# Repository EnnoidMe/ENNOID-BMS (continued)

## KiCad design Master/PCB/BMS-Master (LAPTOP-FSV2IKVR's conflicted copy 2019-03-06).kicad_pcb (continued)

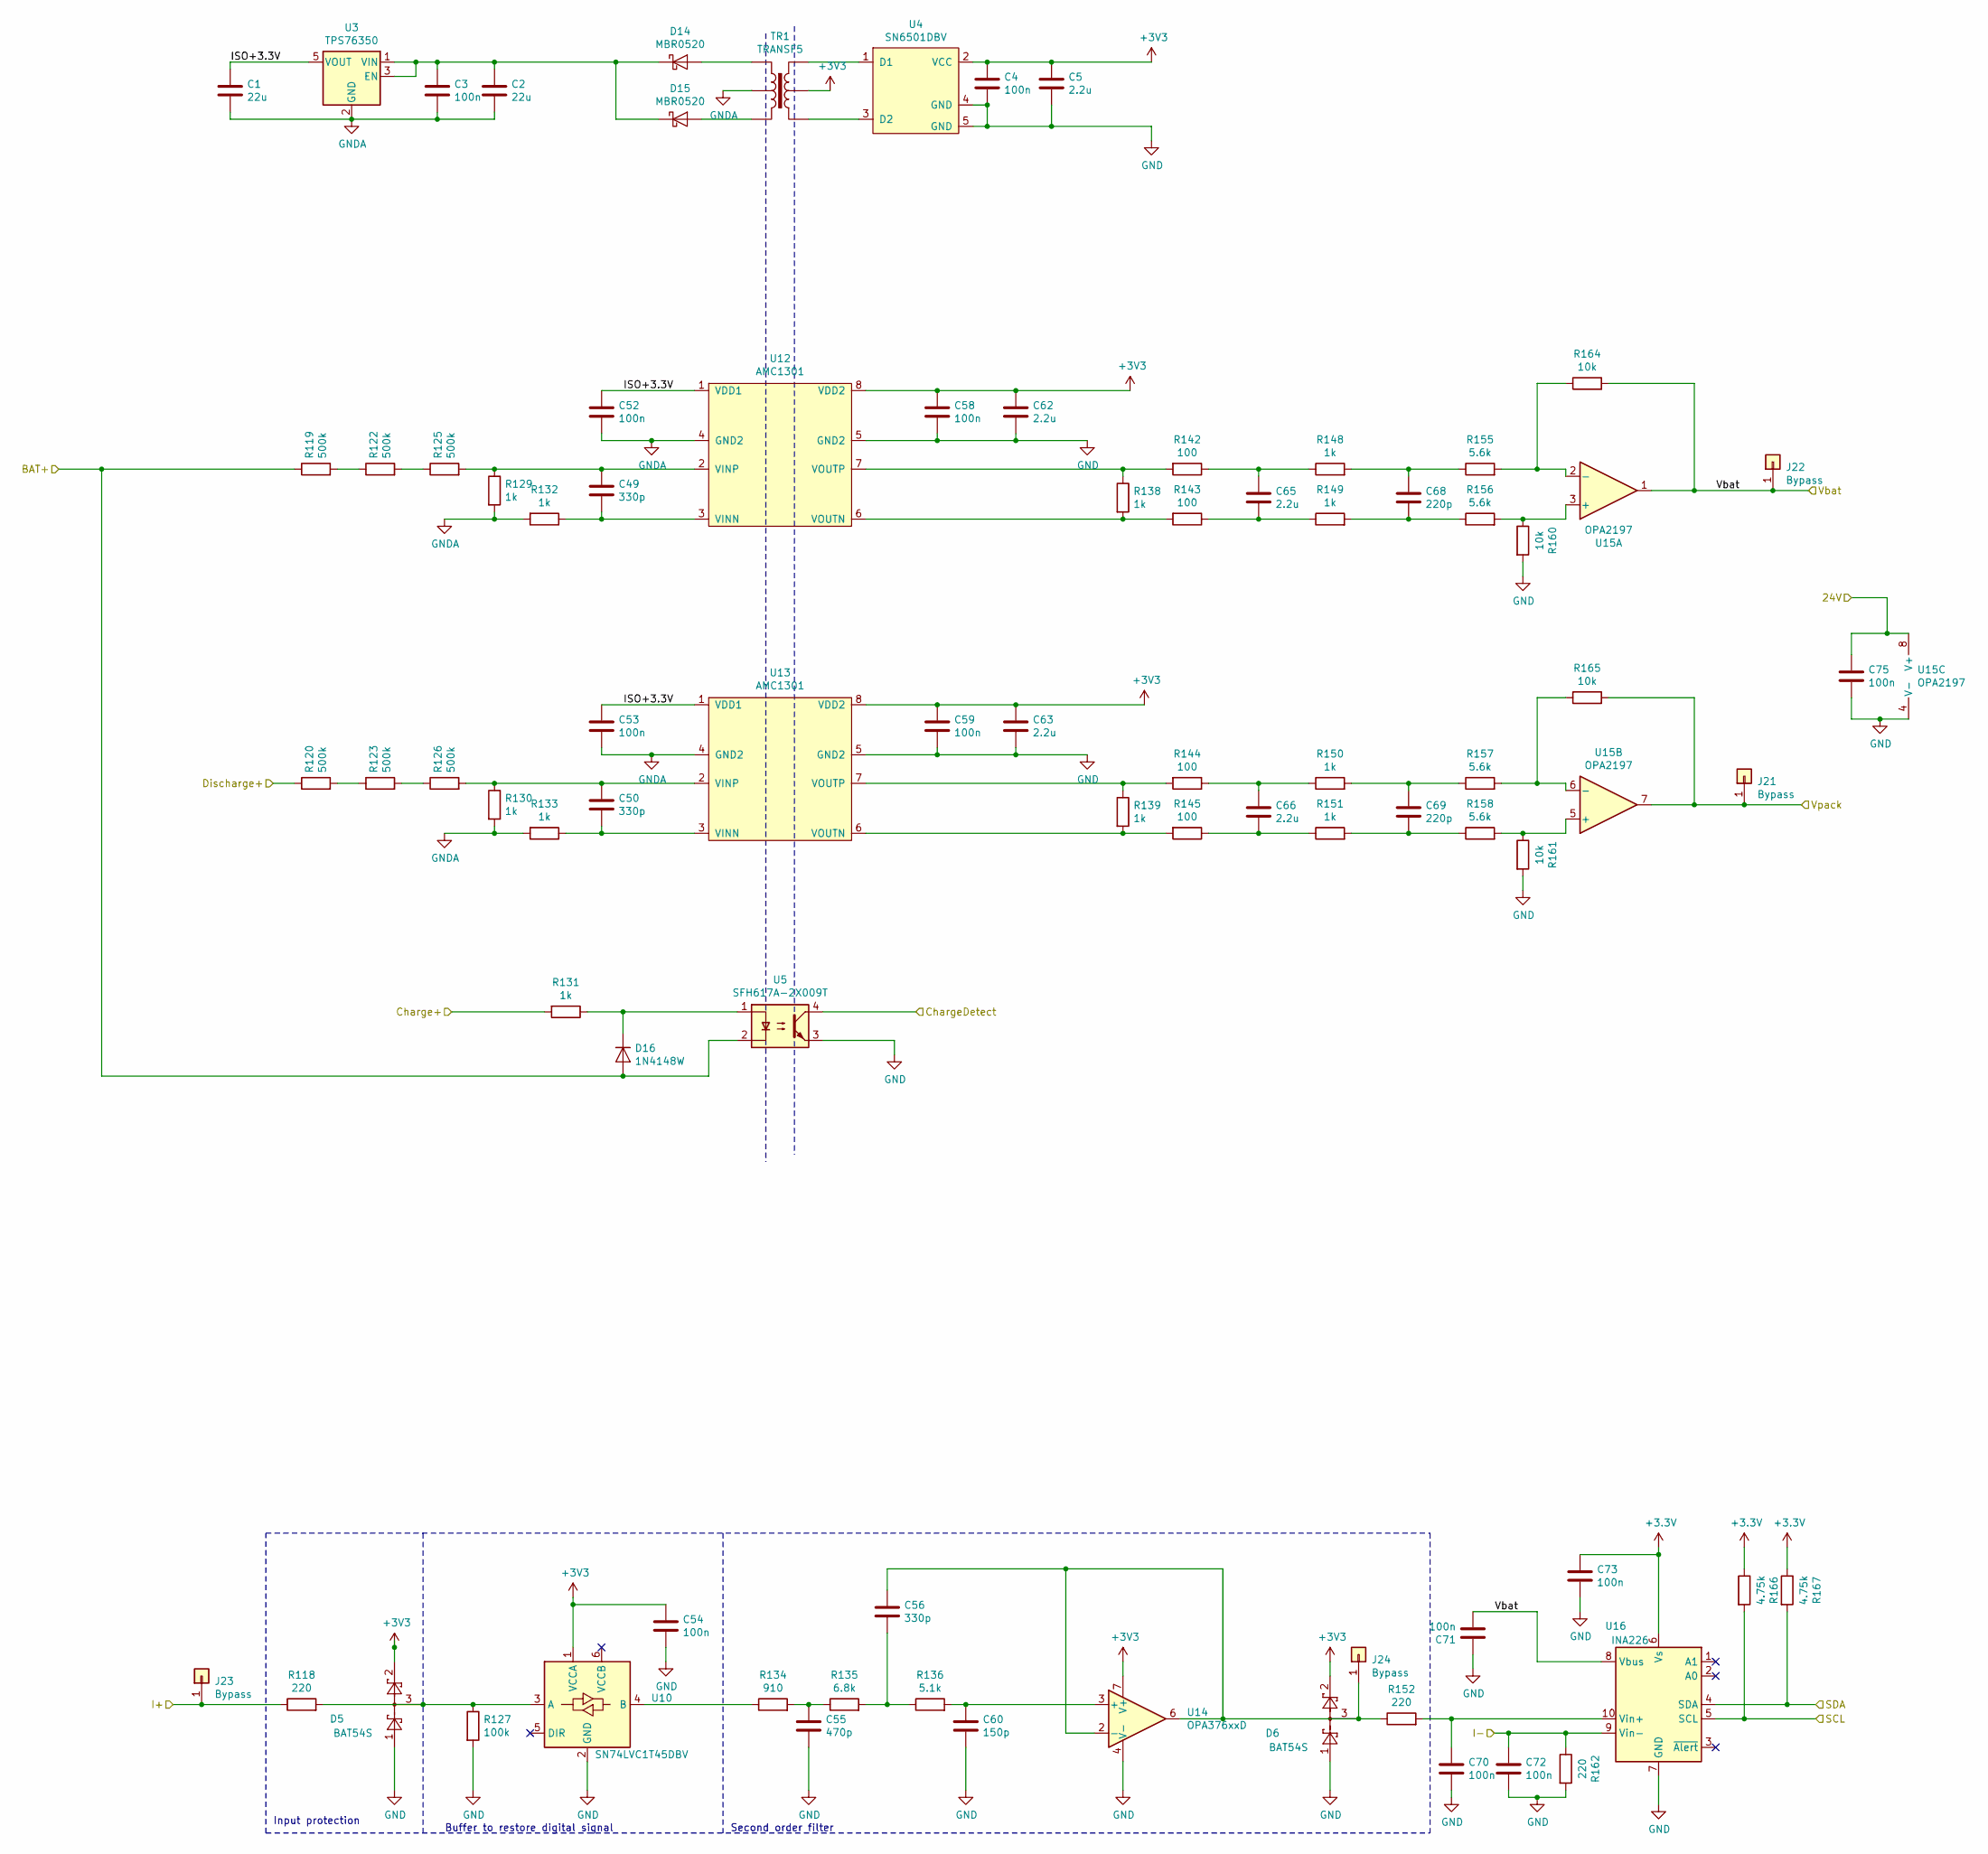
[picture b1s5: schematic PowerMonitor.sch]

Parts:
C1, C2: 22u; C_0805_HandSoldering
C3, C4, C52, C53, C54, C58, C59, C70, C71, C72, C73, C75: 100n; C_0603_HandSoldering
C5, C62, C63, C65, C66: 2.2u; C_0603_HandSoldering
C49, C50, C56: 330p; C_0603_HandSoldering
C55: 470p; C_0603_HandSoldering
C60: 150p; C_0603_HandSoldering
C68, C69: 220p; C_0603_HandSoldering
D5, D6: BAT54S; SOT-23
D14, D15: MBR0520; D_SOD-123
D16: 1N4148W; D_SOD-123
J21, J22, J23, J24: Bypass; TestPoint_Loop_D2.54mm_Drill1.5mm_Beaded
R118, R152, R162: 220; R_0603_HandSoldering
R119, R120, R122, R123, R125, R126: 500k; R_1206
R127: 100k; R_0603_HandSoldering
R129, R130, R131, R132, R133, R138, R139, R148, R149, R150, R151: 1k; R_0603_HandSoldering
R134: 910; R_0603_HandSoldering
R135: 6.8k; R_0603_HandSoldering
R136: 5.1k; R_0603_HandSoldering
R142, R143, R144, R145: 100; R_0603_HandSoldering
R155, R156, R157, R158: 5.6k; R_0603_HandSoldering
R160, R161, R164, R165: 10k; R_0603_HandSoldering
R166, R167: 4.75k; R_0603_HandSoldering
TR1: TRANSF5; WURTH-760390014
U3: TPS76350; SOT-23-5_HandSoldering
U4: SN6501DBV; SOT-23-5_HandSoldering
U5: SFH617A-2X009T; SMDIP-4_W7.62mm
U10: SN74LVC1T45DBV; SOT-23-6
U12, U13: AMC1301; SSO-8_6.8x5.9mm_Pitch1.27mm_Clearance8mm
U14: OPA376xxD; SOIC-8_3.9x4.9mm_Pitch1.27mm
U15: OPA2197; SOIC-8_3.9x4.9mm_Pitch1.27mm
U16: INA226; MSOP-10_3x3mm_Pitch0.5mm

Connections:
/MCU/ChargeDetect: U5.4; also elsewhere on the board
/MCU/SCL: R166.2, U16.5 (SCL); also elsewhere on the board
/MCU/SDA: R167.2, U16.4 (SDA); also elsewhere on the board
/PowerMonitor/24V: C75.1, U15.8 (V+); also elsewhere on the board
/PowerMonitor/BAT+: D16.2 (A), R119.1, U5.2; also elsewhere on the board
/PowerMonitor/Charge+: R131.2; also elsewhere on the board
/PowerMonitor/Discharge+: R120.1; also elsewhere on the board
/PowerMonitor/I: J23.1, R118.1; also elsewhere on the board
/PowerMonitor/ISO+3.3V: C1.1, C52.1, C53.1, U3.5 (VOUT), U12.1 (VDD1), U13.1 (VDD1)
/PowerMonitor/Vbat: C71.1, J22.1, R164.2, U15.1, U16.8 (Vbus); also elsewhere on the board
/PowerMonitor/Vpack: J21.1, R165.2, U15.7; also elsewhere on the board
GND: C4.2, C5.2, C54.1, C55.1, C58.2, C59.2, C60.1, C62.2, C63.2, C70.1, C71.2, C72.1, C73.1, C75.2, D5.1, D6.1, R127.2, R160.2, R161.2, R162.2, U4.4 (GND), U4.5 (GND), U5.3, U10.2 (GND), U12.5 (GND2), U13.5 (GND2), U14.4 (V-), U15.4 (V-), U16.7 (GND); also elsewhere on the board
GNDA: C1.2, C2.2, C3.2, C52.2, C53.2, R129.2, R130.2, R132.2, R133.2, TR1.2, U3.2 (GND), U12.4 (GND2), U13.4 (GND2); also elsewhere on the board
unnamed: C2.1, C3.1, D14.1 (K), D15.1 (K), U3.1 (VIN), U3.3 (EN)
unnamed: C49.1, R125.2, R129.1, U12.2 (VINP)
unnamed: C49.2, R132.1, U12.3 (VINN)
unnamed: C50.1, R126.2, R130.1, U13.2 (VINP)
unnamed: C50.2, R133.1, U13.3 (VINN)
unnamed: C55.2, R134.2, R135.1
unnamed: C56.1, R135.2, R136.1
unnamed: C56.2, D6.3, J24.1, R152.1, U14.2 (-), U14.6
unnamed: C60.2, R136.2, U14.3 (+)
unnamed: C65.1, R142.1, R148.1
unnamed: C65.2, R143.1, R149.1
unnamed: C66.1, R144.1, R150.1
unnamed: C66.2, R145.1, R151.1
unnamed: C68.1, R148.2, R155.1
unnamed: C68.2, R149.2, R156.1
unnamed: C69.1, R150.2, R157.1
unnamed: C69.2, R151.2, R158.1
unnamed: C70.2, R152.2, U16.10 (Vin+)
unnamed: C72.2, R162.1, U16.9 (Vin-)
unnamed: D5.3, R118.2, R127.1, U10.3 (A)
unnamed: D14.2 (A), TR1.1
unnamed: D15.2 (A), TR1.3
unnamed: D16.1 (K), R131.1, U5.1
unnamed: R119.2, R122.1
unnamed: R120.2, R123.1
unnamed: R122.2, R125.1
unnamed: R123.2, R126.1
unnamed: R134.1, U10.4 (B)
unnamed: R138.1, R142.2, U12.7 (VOUTP)
unnamed: R138.2, R143.2, U12.6 (VOUTN)
unnamed: R139.1, R144.2, U13.7 (VOUTP)
unnamed: R139.2, R145.2, U13.6 (VOUTN)
unnamed: R155.2, R164.1, U15.2 (-)
unnamed: R156.2, R160.1, U15.3 (+)
unnamed: R157.2, R165.1, U15.6 (-)
unnamed: R158.2, R161.1, U15.5 (+)
unnamed: TR1.4, U4.3 (D2)
unnamed: TR1.6, U4.1 (D1)

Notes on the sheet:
Input protection
Buffer to restore digital signal
Second order filter

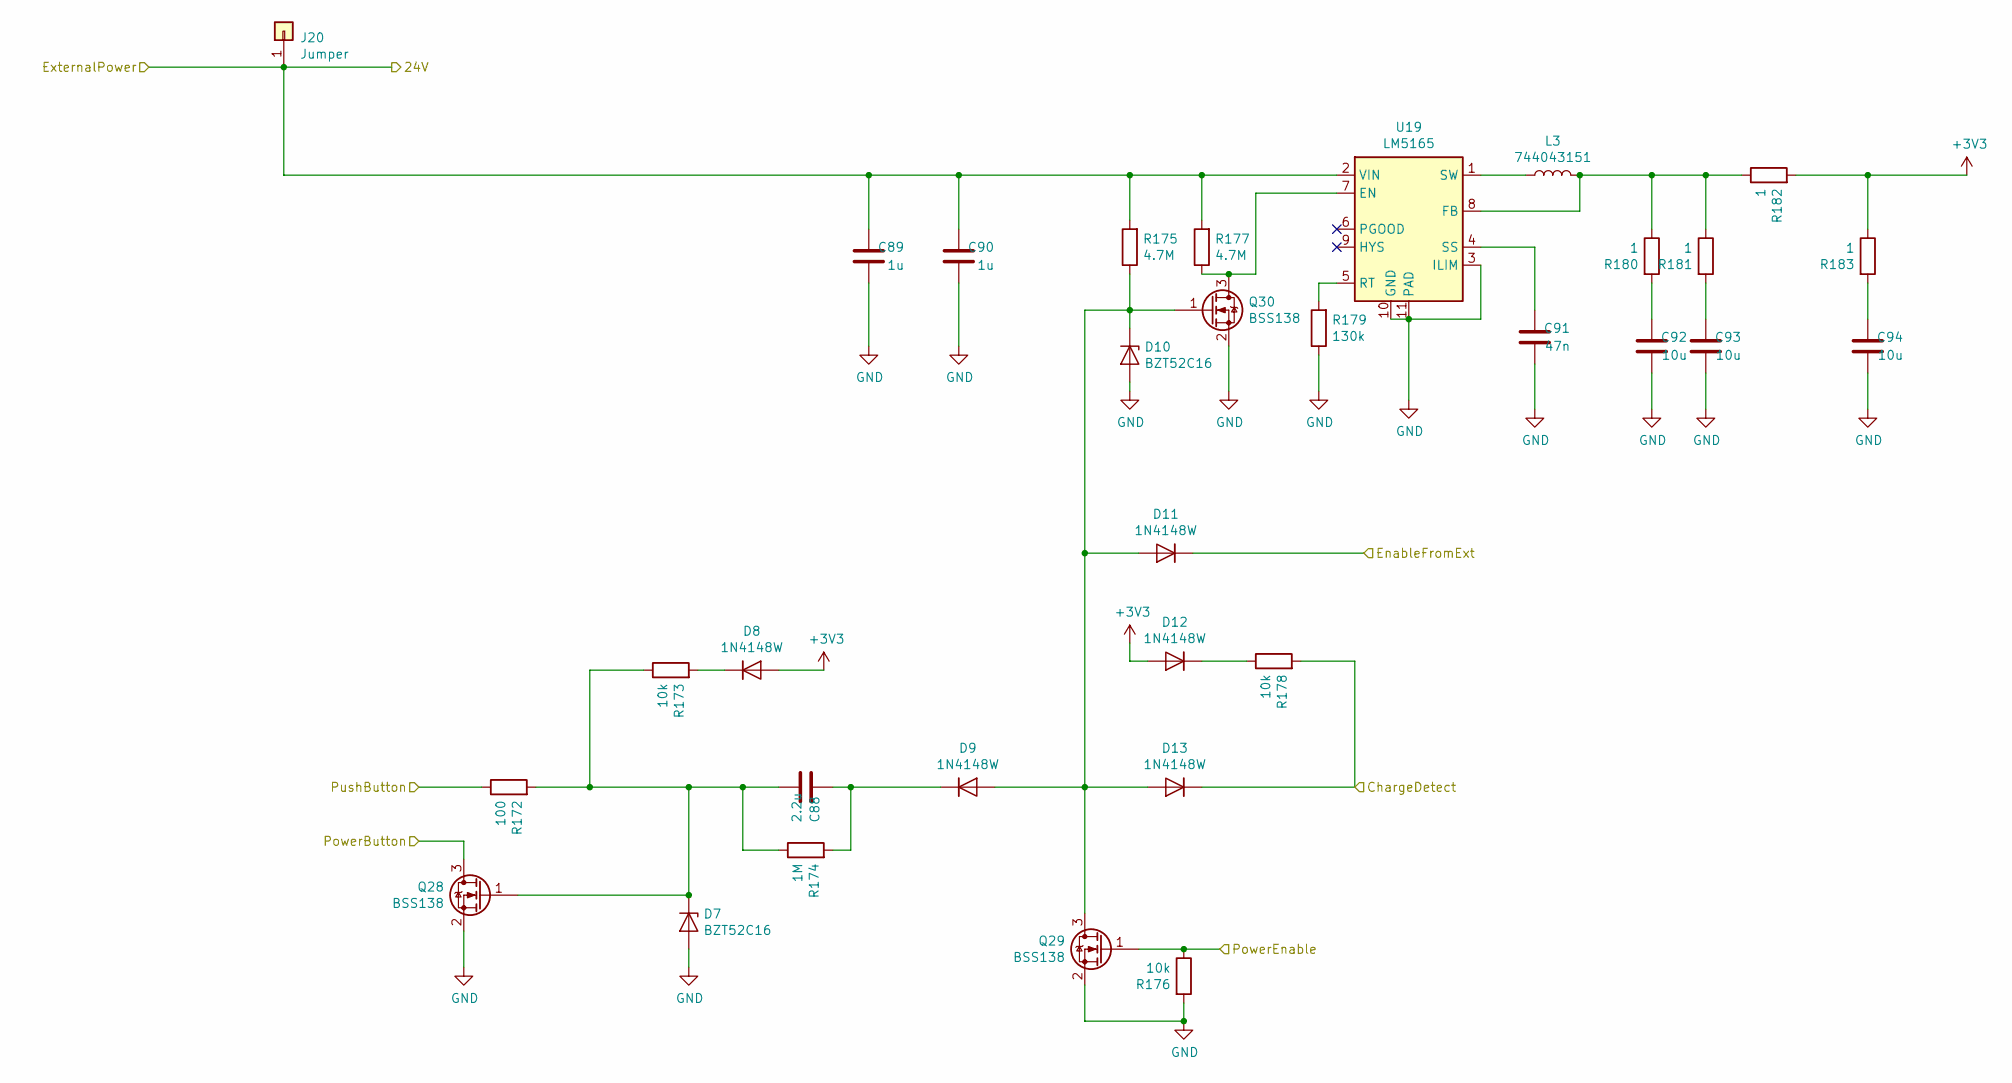
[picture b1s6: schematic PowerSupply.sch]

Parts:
C88: 2.2u; C_0603_HandSoldering
C89, C90: 1u; C_0603_HandSoldering
C91: 47n; C_0603_HandSoldering
C92, C93, C94: 10u; C_0603_HandSoldering
D7, D10: BZT52C16; D_SOD-123
D8, D9, D11, D12, D13: 1N4148W; D_SOD-123
J20: Jumper; TestPoint_Loop_D2.54mm_Drill1.5mm_Beaded
L3: 744043151; L_Wuerth_WE-PD2-Typ-MS
Q28, Q29, Q30: BSS138; SOT-23
R172: 100; R_0603_HandSoldering
R173, R176, R178: 10k; R_0603_HandSoldering
R174: 1M; R_0603_HandSoldering
R175, R177: 4.7M; R_0805_HandSoldering
R179: 130k; R_0603_HandSoldering
R180, R181, R182, R183: 1; R_0603_HandSoldering
U19: LM5165; Texas_S-PVSON-N10_ThermalVias

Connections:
/MCU/ChargeDetect: D13.1 (K), R178.2; also elsewhere on the board
/MCU/PowerButton: Q28.3 (D); also elsewhere on the board
/MCU/PowerEnable: Q29.1 (G), R176.1; also elsewhere on the board
/PowerMonitor/24V: C89.2, C90.2, J20.1, R175.2, R177.2, U19.2 (VIN); also elsewhere on the board
/PowerSupply/EnableFromExt: D11.1 (K); also elsewhere on the board
/PowerSupply/PushButton: R172.1; also elsewhere on the board
GND: C89.1, C90.1, C91.1, C92.1, C93.1, C94.1, D7.2 (A), D10.2 (A), Q28.2 (S), Q29.2 (S), Q30.2 (S), R176.2, R179.1, U19.3 (ILIM), U19.10 (GND), U19.11 (PAD); also elsewhere on the board
unnamed: C88.1, D7.1 (K), Q28.1 (G), R172.2, R173.1, R174.1
unnamed: C88.2, D9.1 (K), R174.2
unnamed: C91.2, U19.4 (SS)
unnamed: C92.2, R180.2
unnamed: C93.2, R181.2
unnamed: C94.2, R183.2
unnamed: D8.1 (K), R173.2
unnamed: D9.2 (A), D10.1 (K), D11.2 (A), D13.2 (A), Q29.3 (D), Q30.1 (G), R175.1
unnamed: D12.1 (K), R178.1
unnamed: L3.1, U19.1 (SW)
unnamed: L3.2, R180.1, R181.1, R182.1, U19.8 (FB)
unnamed: Q30.3 (D), R177.1, U19.7 (EN)
unnamed: R179.2, U19.5 (RT)

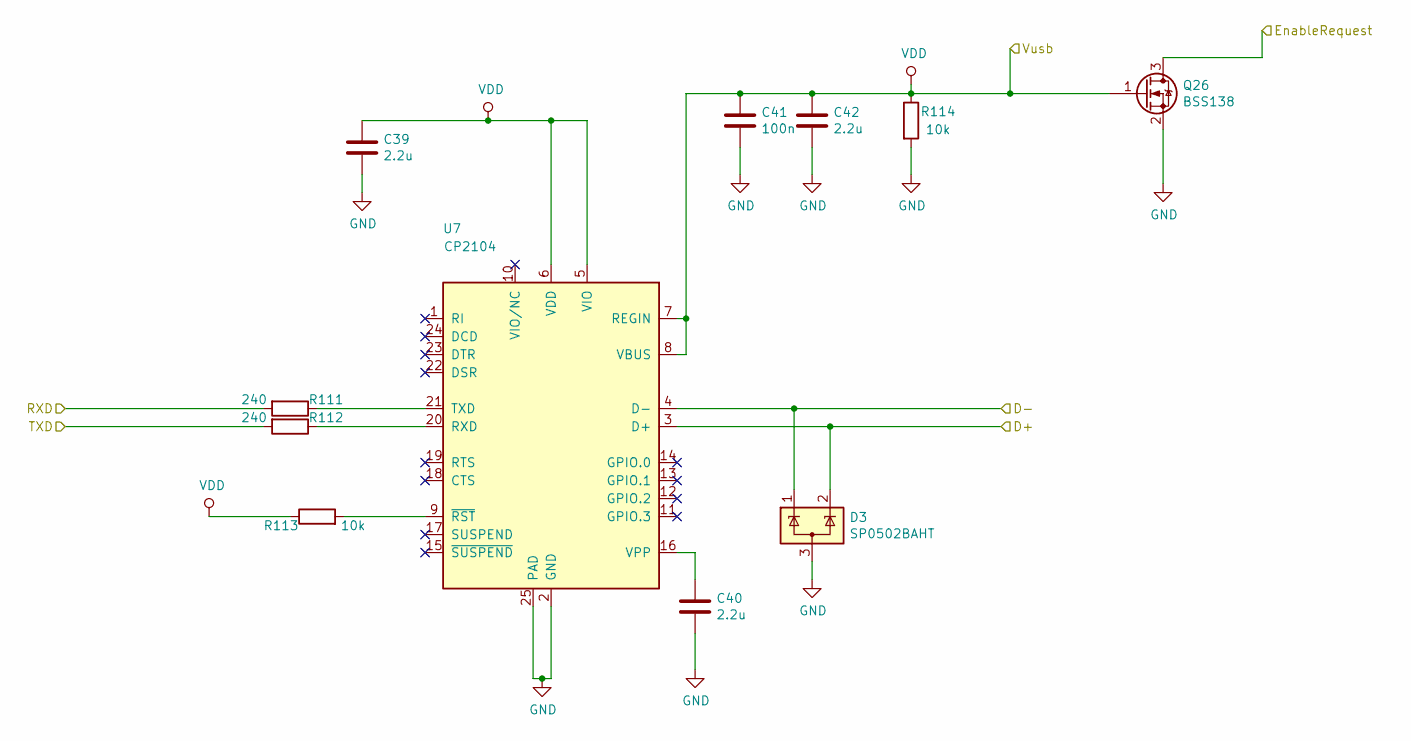
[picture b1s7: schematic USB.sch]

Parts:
C39, C40, C42: 2.2u; C_0603_HandSoldering
C41: 100n; C_0603_HandSoldering
D3: SP0502BAHT; SOT-23
Q26: BSS138; SOT-23
R111, R112: 240; R_0603_HandSoldering
R113, R114: 10k; R_0603_HandSoldering
U7: CP2104; QFN-24-1EP_4x4mm_Pitch0.5mm

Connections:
/PowerSupply/EnableFromExt: Q26.3 (D); also elsewhere on the board
/USB/D+: D3.2 (K), U7.3 (D+); also elsewhere on the board
/USB/D-: D3.1 (K), U7.4 (D-); also elsewhere on the board
/USB/RXD: R111.2; also elsewhere on the board
/USB/TXD: R112.2; also elsewhere on the board
GND: C39.2, C40.2, C41.2, C42.2, D3.3 (A), Q26.2 (S), R114.2, U7.2 (GND), U7.25 (PAD); also elsewhere on the board
unnamed: C40.1, U7.16 (VPP)
unnamed: R111.1, U7.21 (TXD)
unnamed: R112.1, U7.20 (RXD)
unnamed: R113.2, U7.9 (~RST)
VDD: C39.1, C41.1, C42.1, Q26.1 (G), R113.1, R114.1, U7.5 (VIO), U7.6 (VDD), U7.7 (REGIN), U7.8 (VBUS); also elsewhere on the board

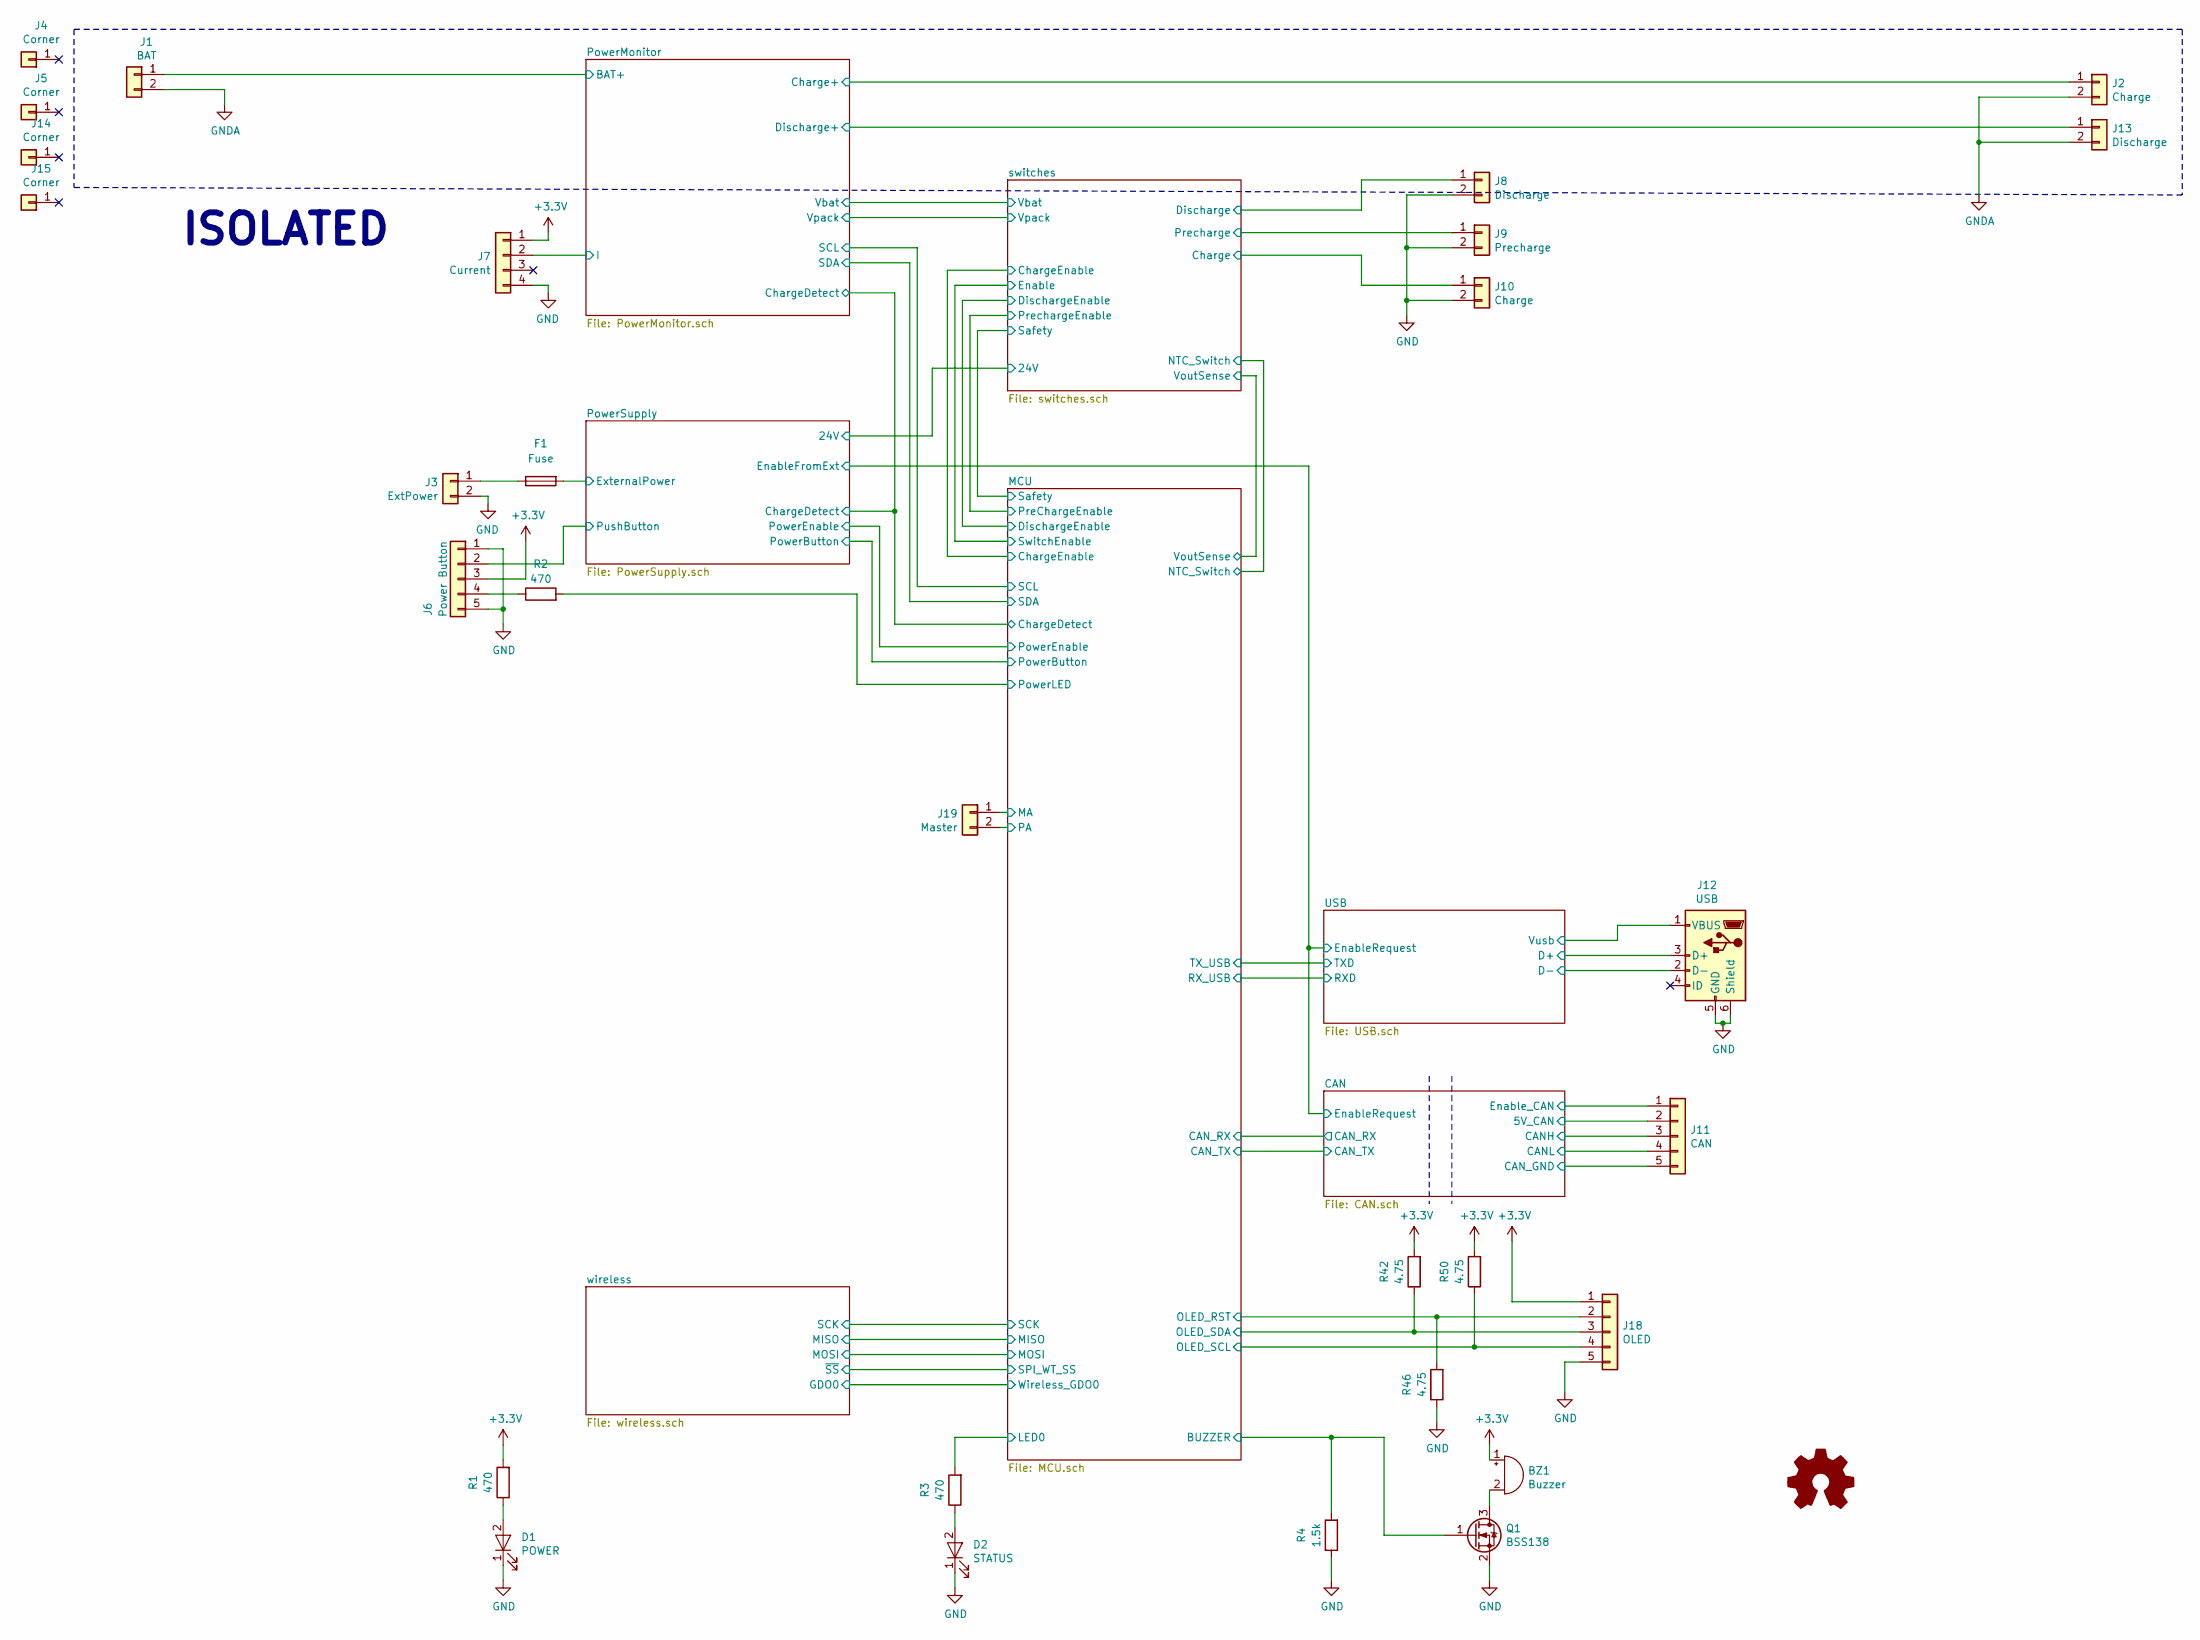
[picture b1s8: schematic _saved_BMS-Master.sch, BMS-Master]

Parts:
BZ1: Buzzer; PUIAudio_SMT_0825_S_4_R
D1: POWER; LED_0603_HandSoldering
D2: STATUS; LED_0603_HandSoldering
F1: Fuse; Fuse_SMD1206_HandSoldering
J1: BAT; TerminalBlock_RND_205-00001_Pitch5.00mm
J2: Charge; TerminalBlock_RND_205-00001_Pitch5.00mm
J3: ExtPower; Molex_KK-6410-02_02x2.54mm_Straight
J4, J5, J14, J15: Corner; MountingHole_2.7mm_M2.5_Pad_Via
J6: Power Button; Molex_PicoBlade_53398-0571_05x1.25mm_Straight
J7: Current; Molex_KK-6410-04_04x2.54mm_Straight
J8: Discharge; Molex_KK-6410-02_02x2.54mm_Straight
J9: Precharge; Molex_KK-6410-02_02x2.54mm_Straight
J10: Charge; Molex_KK-6410-02_02x2.54mm_Straight
J11: CAN; Molex_PicoBlade_53261-0571_05x1.25mm_Angled
J12: USB; USB_Micro-B_Molex_47346-0001
J13: Discharge; TerminalBlock_RND_205-00001_Pitch5.00mm
J18: OLED; Molex_PicoBlade_53398-0571_05x1.25mm_Straight
J19: Master; Molex_KK-6410-02_02x2.54mm_Straight
LOGO1: Logo_Open_Hardware_Small; ENNOID-LOGO
Q1: BSS138; SOT-23
R1, R2, R3: 470; R_0603_HandSoldering
R4: 1.5k; R_0603_HandSoldering
R42, R46, R50: 4.75; R_0603_HandSoldering

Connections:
/CAN/5V_CAN: J11.2; also elsewhere on the board
/CAN/CANH: J11.3; also elsewhere on the board
/CAN/CANL: J11.4; also elsewhere on the board
/CAN/CAN_GND: J11.5; also elsewhere on the board
/CAN/Enable_CAN: J11.1; also elsewhere on the board
/MCU/BUZZER: Q1.1 (G), R4.2; also elsewhere on the board
/MCU/LED0: R3.2; also elsewhere on the board
/MCU/MA: J19.1; also elsewhere on the board
/MCU/OLED_RST: J18.2, R46.2; also elsewhere on the board
/MCU/OLED_SCL: J18.4, R50.1; also elsewhere on the board
/MCU/OLED_SDA: J18.3, R42.1; also elsewhere on the board
/MCU/PA: J19.2; also elsewhere on the board
/MCU/PowerLED: R2.2; also elsewhere on the board
/PowerMonitor/24V: F1.2; also elsewhere on the board
/PowerMonitor/BAT+: J1.1; also elsewhere on the board
/PowerMonitor/Charge+: J2.1; also elsewhere on the board
/PowerMonitor/Discharge+: J13.1; also elsewhere on the board
/PowerMonitor/I: J7.2; also elsewhere on the board
/PowerSupply/PushButton: J6.2; also elsewhere on the board
/USB/D+: J12.3 (D+); also elsewhere on the board
/USB/D-: J12.2 (D-); also elsewhere on the board
/switches/Charge: J10.1; also elsewhere on the board
/switches/Discharge: J8.1; also elsewhere on the board
/switches/Precharge: J9.1; also elsewhere on the board
GND: D1.1 (K), D2.1 (K), J3.2, J6.1, J6.5, J7.4, J8.2, J9.2, J10.2, J12.5 (GND), J12.6 (Shield), J18.5, Q1.2 (S), R4.1, R46.1; also elsewhere on the board
GNDA: J1.2, J2.2, J13.2; also elsewhere on the board
unnamed: BZ1.2 (+), Q1.3 (D)
unnamed: D1.2 (A), R1.1
unnamed: D2.2 (A), R3.1
unnamed: F1.1, J3.1
unnamed: J6.4, R2.1
VDD: J12.1 (VBUS); also elsewhere on the board

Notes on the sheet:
ISOLATED

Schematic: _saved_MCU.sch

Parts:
C20: 1uF; C_0603_HandSoldering
C76: 18p; C_0603_HandSoldering; Voltage 50V
C77: 18p; R_0603_HandSoldering; Voltage 50V
C78: 100n; C_0603_HandSoldering
C79: C; C_0603_HandSoldering
C80, C81, C82, C83, C84: 100n; C_0603_HandSoldering; Voltage 25V
J16: SD; Hirose_DM3AT-SF-PEJM5
J17: DEBUG; Molex_PicoBlade_53261-0571_05x1.25mm_Angled
L1: BLM18PG330SN1D; L_0603_HandSoldering
Q27: BSS138; SOT-23
R5, R36, R170: 1k; R_0603_HandSoldering
R37, R168, R169: 10k; R_0603_HandSoldering
U2: LTC6820; MSOP-16_3x4mm_Pitch0.5mm
U17: STM32F303CCTx; LQFP-48_7x7mm_Pitch0.5mm
Y1: 8MHz; Crystal_SMD_Abracon_ABM3-2pin_5.0x3.2mm

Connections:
/CAN/CAN_RX: U17.32 (ADC1_EXTI11/ADC2_EXTI11/CAN_RX/COMP1_OU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); also elsewhere on the board
/CAN/CAN_TX: U17.33 (CAN_TX/COMP2_OUT/TIM16_CH1/TIM1_CH2N/TI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); also elsewhere on the board
/MCU/BUZZER: U17.38 (ADC1_EXTI15/ADC2_EXTI15/I2C1_SCL/I2S3_W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); also elsewhere on the board
/MCU/ChargeDetect: Q27.1 (G); also elsewhere on the board
/MCU/LED0: U17.19 (PB1/ADC3_IN1/COMP4_OUT/OPAMP3_VOUT/TIM1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); also elsewhere on the board
/MCU/MISO: R37.2, U2.3 (MISO), U17.16 (ADC2_IN3/COMP1_OUT/OPAMP2_VOUT/SPI1_MIS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); also elsewhere on the board
/MCU/MOSI: U2.2 (MOSI), U17.17 (ADC2_IN4/COMP2_INP/COMP2_OUT/OPAMP1_VIN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); also elsewhere on the board
/MCU/NRST: C78.1, J17.5, R168.2, U17.7 (NRST)
/MCU/NTC_Switch: C84.2, R170.2, U17.10 (ADC1_IN1/COMP1_INM/COMP1_OUT/COMP7_INP/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); also elsewhere on the board
/MCU/OLED_RST: U17.45 (PB8/CAN_RX/COMP1_OUT/I2C1_SCL/TIM16_CH1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); also elsewhere on the board
/MCU/OLED_SCL: U17.42 (PB6/I2C1_SCL/TIM16_CH1N/TIM4_CH1/TIM8_B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); also elsewhere on the board
/MCU/OLED_SDA: U17.43 (PB7/I2C1_SDA/TIM17_CH1N/TIM3_CH4/TIM4_C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); also elsewhere on the board
/MCU/PowerButton: U17.40 (PB4/I2S3_ext_SD/SPI1_MISO/SPI3_MISO/SYS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); also elsewhere on the board
/MCU/PowerEnable: U17.41 (PB5/I2C1_SMBA/I2S3_SD/SPI1_MOSI/SPI3_MO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); also elsewhere on the board
/MCU/PowerLED: U17.39 (PB3/I2S3_CK/SPI1_SCK/SPI3_SCK/SYS_JTDO-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); also elsewhere on the board
/MCU/PreChargeEnable: U17.22 (PB11/ADC1_EXTI11/ADC2_EXTI11/COMP6_INP/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); also elsewhere on the board
/MCU/SCK: U2.4 (SCK), U17.15 (ADC2_IN2/COMP1_INM/COMP2_INM/COMP3_INM/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); also elsewhere on the board
/MCU/SCL: U17.30 (COMP5_OUT/DAC_EXTI9/I2C2_SCL/I2S3_MCK/T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); also elsewhere on the board
/MCU/SDA: U17.31 (COMP6_OUT/I2C2_SDA/TIM17_BKIN/TIM1_CH3/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); also elsewhere on the board
/MCU/SDCardDetect: J16.9 (DET_B), U17.46 (PB9/CAN_TX/COMP2_OUT/DAC_EXTI9/I2C1_SDA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)
/MCU/SPI_WT_SS: U17.29 (COMP3_OUT/I2C2_SMBA/I2S2_MCK/RCC_MCO/TI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); also elsewhere on the board
/MCU/SS: U2.5 (CSB), U17.14 (ADC2_IN1/COMP1_INM/COMP2_INM/COMP3_INM/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)
/MCU/SWCLK: J17.2, U17.37 (I2C1_SDA/SYS_JTCK-SWCLK/TIM1_BKIN/TIM8_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)
/MCU/SWDIO: J17.4, U17.34 (IR_OUT/SYS_JTMS-SWDIO/TIM16_CH1N/TIM4_C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)
/MCU/Safety: U17.2 (PC13/RTC_OUT_ALARM/RTC_OUT_CALIB/RTC_TA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); also elsewhere on the board
/MCU/VoutSense: U17.11 (ADC1_IN2/COMP1_INP/OPAMP1_VINP/OPAMP1_V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); also elsewhere on the board
/USB/RXD: U17.13 (ADC1_IN4/COMP2_INP/OPAMP1_VINM/OPAMP1_V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); also elsewhere on the board
/USB/TXD: U17.12 (ADC1_IN3/ADC3_EXTI2/ADC4_EXTI2/COMP2_IN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); also elsewhere on the board
/switches/Enable: R169.1, U17.20 (PB2/ADC2_IN12/ADC3_EXTI2/ADC4_EXTI2/COM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); also elsewhere on the board
/wireless/GDO0: U17.4 (PC15/ADC1_EXTI15/ADC2_EXTI15/RCC_OSC32_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); also elsewhere on the board
GND: C20.1, C76.2, C77.2, C78.2, C79.2, C80.2, C81.2, C82.2, C83.2, C84.1, J16.6 (VSS), J16.10 (DET_A), J16.11 (SHIELD), J17.3, Q27.2 (S), R5.2, R169.2, U2.13 (SLOW), U2.14 (GND), U17.8 (VSSA), U17.23 (VSS), U17.35 (VSS), U17.44 (BOOT0), U17.47 (VSS); also elsewhere on the board
unnamed: C76.1, U17.5 (PF0/I2C2_SDA/RCC_OSC_IN/TIM1_CH3N), Y1.1
unnamed: C77.1, U17.6 (PF1/I2C2_SCL/RCC_OSC_OUT), Y1.2
unnamed: C79.1, J16.4 (VDD), L1.1
unnamed: J16.2 (DAT3/CD), U17.25 (PB12/ADC4_IN3/COMP3_INM/I2C2_SMBA/I2S2_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)
unnamed: J16.3 (CMD), U17.28 (PB15/ADC1_EXTI15/ADC2_EXTI15/ADC4_IN5/C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)
unnamed: J16.5 (CLK), U17.26 (PB13/ADC3_IN5/COMP5_INP/I2S2_CK/OPAMP3_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)
unnamed: J16.7 (DAT0), U17.27 (PB14/ADC4_IN4/COMP3_INP/I2S2_ext_SD/OPA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)
unnamed: Q27.3 (D), U17.3 (PC14/RCC_OSC32_IN)
unnamed 120: U2.11 (IP); also elsewhere on the board
unnamed 121: U2.10 (IM); also elsewhere on the board
unnamed: R36.1, U2.16 (IBIAS)
unnamed: R5.1, R36.2, U2.15 (ICMP)

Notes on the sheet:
DEBUG

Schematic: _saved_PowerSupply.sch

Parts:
C88: 2.2u; C_0603_HandSoldering
C89, C90: 1u; C_0603_HandSoldering
C91: 47n; C_0603_HandSoldering
C92, C93, C94: 10u; C_0603_HandSoldering
D7, D10: BZT52C16; D_SOD-123
D8, D9, D11, D12, D13: 1N4148W; D_SOD-123
L3: 744043151; L_Wuerth_WE-PD2-Typ-MS
Q28, Q29, Q30: BSS138; SOT-23
R172: 100; R_0603_HandSoldering
R173, R176, R178: 10k; R_0603_HandSoldering
R174: 1M; R_0603_HandSoldering
R175, R177: 4.7M; R_0805_HandSoldering
R179: 130k; R_0603_HandSoldering
R180, R181, R182, R183: 1; R_0603_HandSoldering
U19: LM5165; Texas_S-PVSON-N10_ThermalVias

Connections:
/MCU/ChargeDetect: D13.1 (K), R178.2; also elsewhere on the board
/MCU/PowerButton: Q28.3 (D); also elsewhere on the board
/MCU/PowerEnable: Q29.1 (G), R176.1; also elsewhere on the board
/PowerMonitor/24V: C89.2, C90.2, R175.2, R177.2, U19.2 (VIN); also elsewhere on the board
/PowerSupply/EnableFromExt: D11.1 (K); also elsewhere on the board
/PowerSupply/PushButton: R172.1; also elsewhere on the board
GND: C89.1, C90.1, C91.1, C92.1, C93.1, C94.1, D7.2 (A), D10.2 (A), Q28.2 (S), Q29.2 (S), Q30.2 (S), R176.2, R179.1, U19.3 (ILIM), U19.10 (GND), U19.11 (PAD); also elsewhere on the board
unnamed: C88.1, D7.1 (K), Q28.1 (G), R172.2, R173.1, R174.1
unnamed: C88.2, D9.1 (K), R174.2
unnamed: C91.2, U19.4 (SS)
unnamed: C92.2, R180.2
unnamed: C93.2, R181.2
unnamed: C94.2, R183.2
unnamed: D8.1 (K), R173.2
unnamed: D9.2 (A), D10.1 (K), D11.2 (A), D13.2 (A), Q29.3 (D), Q30.1 (G), R175.1
unnamed: D12.1 (K), R178.1
unnamed: L3.1, U19.1 (SW)
unnamed: L3.2, R180.1, R181.1, R182.1, U19.8 (FB)
unnamed: Q30.3 (D), R177.1, U19.7 (EN)
unnamed: R179.2, U19.5 (RT)

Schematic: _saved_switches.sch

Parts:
Q2, Q3: BSS138; SOT-23
R23, R24, R25: 10; R_0603_HandSoldering
R27, R28: 4.7M; R_0603_HandSoldering
TH1: Thermistor_NTC; R_0805_HandSoldering

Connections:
/MCU/NTC_Switch: TH1.2; also elsewhere on the board
/MCU/Safety: Q2.1 (G), Q3.1 (G); also elsewhere on the board
/switches/Charge: R28.2; also elsewhere on the board
/switches/Discharge: R27.2; also elsewhere on the board
GND: Q2.2 (S), Q3.2 (S), TH1.1; also elsewhere on the board
unnamed 115: R25.2, R28.1; also elsewhere on the board
unnamed 116: R23.2; also elsewhere on the board
unnamed 117: R24.2, R27.1; also elsewhere on the board
unnamed 127: R24.1; also elsewhere on the board

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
